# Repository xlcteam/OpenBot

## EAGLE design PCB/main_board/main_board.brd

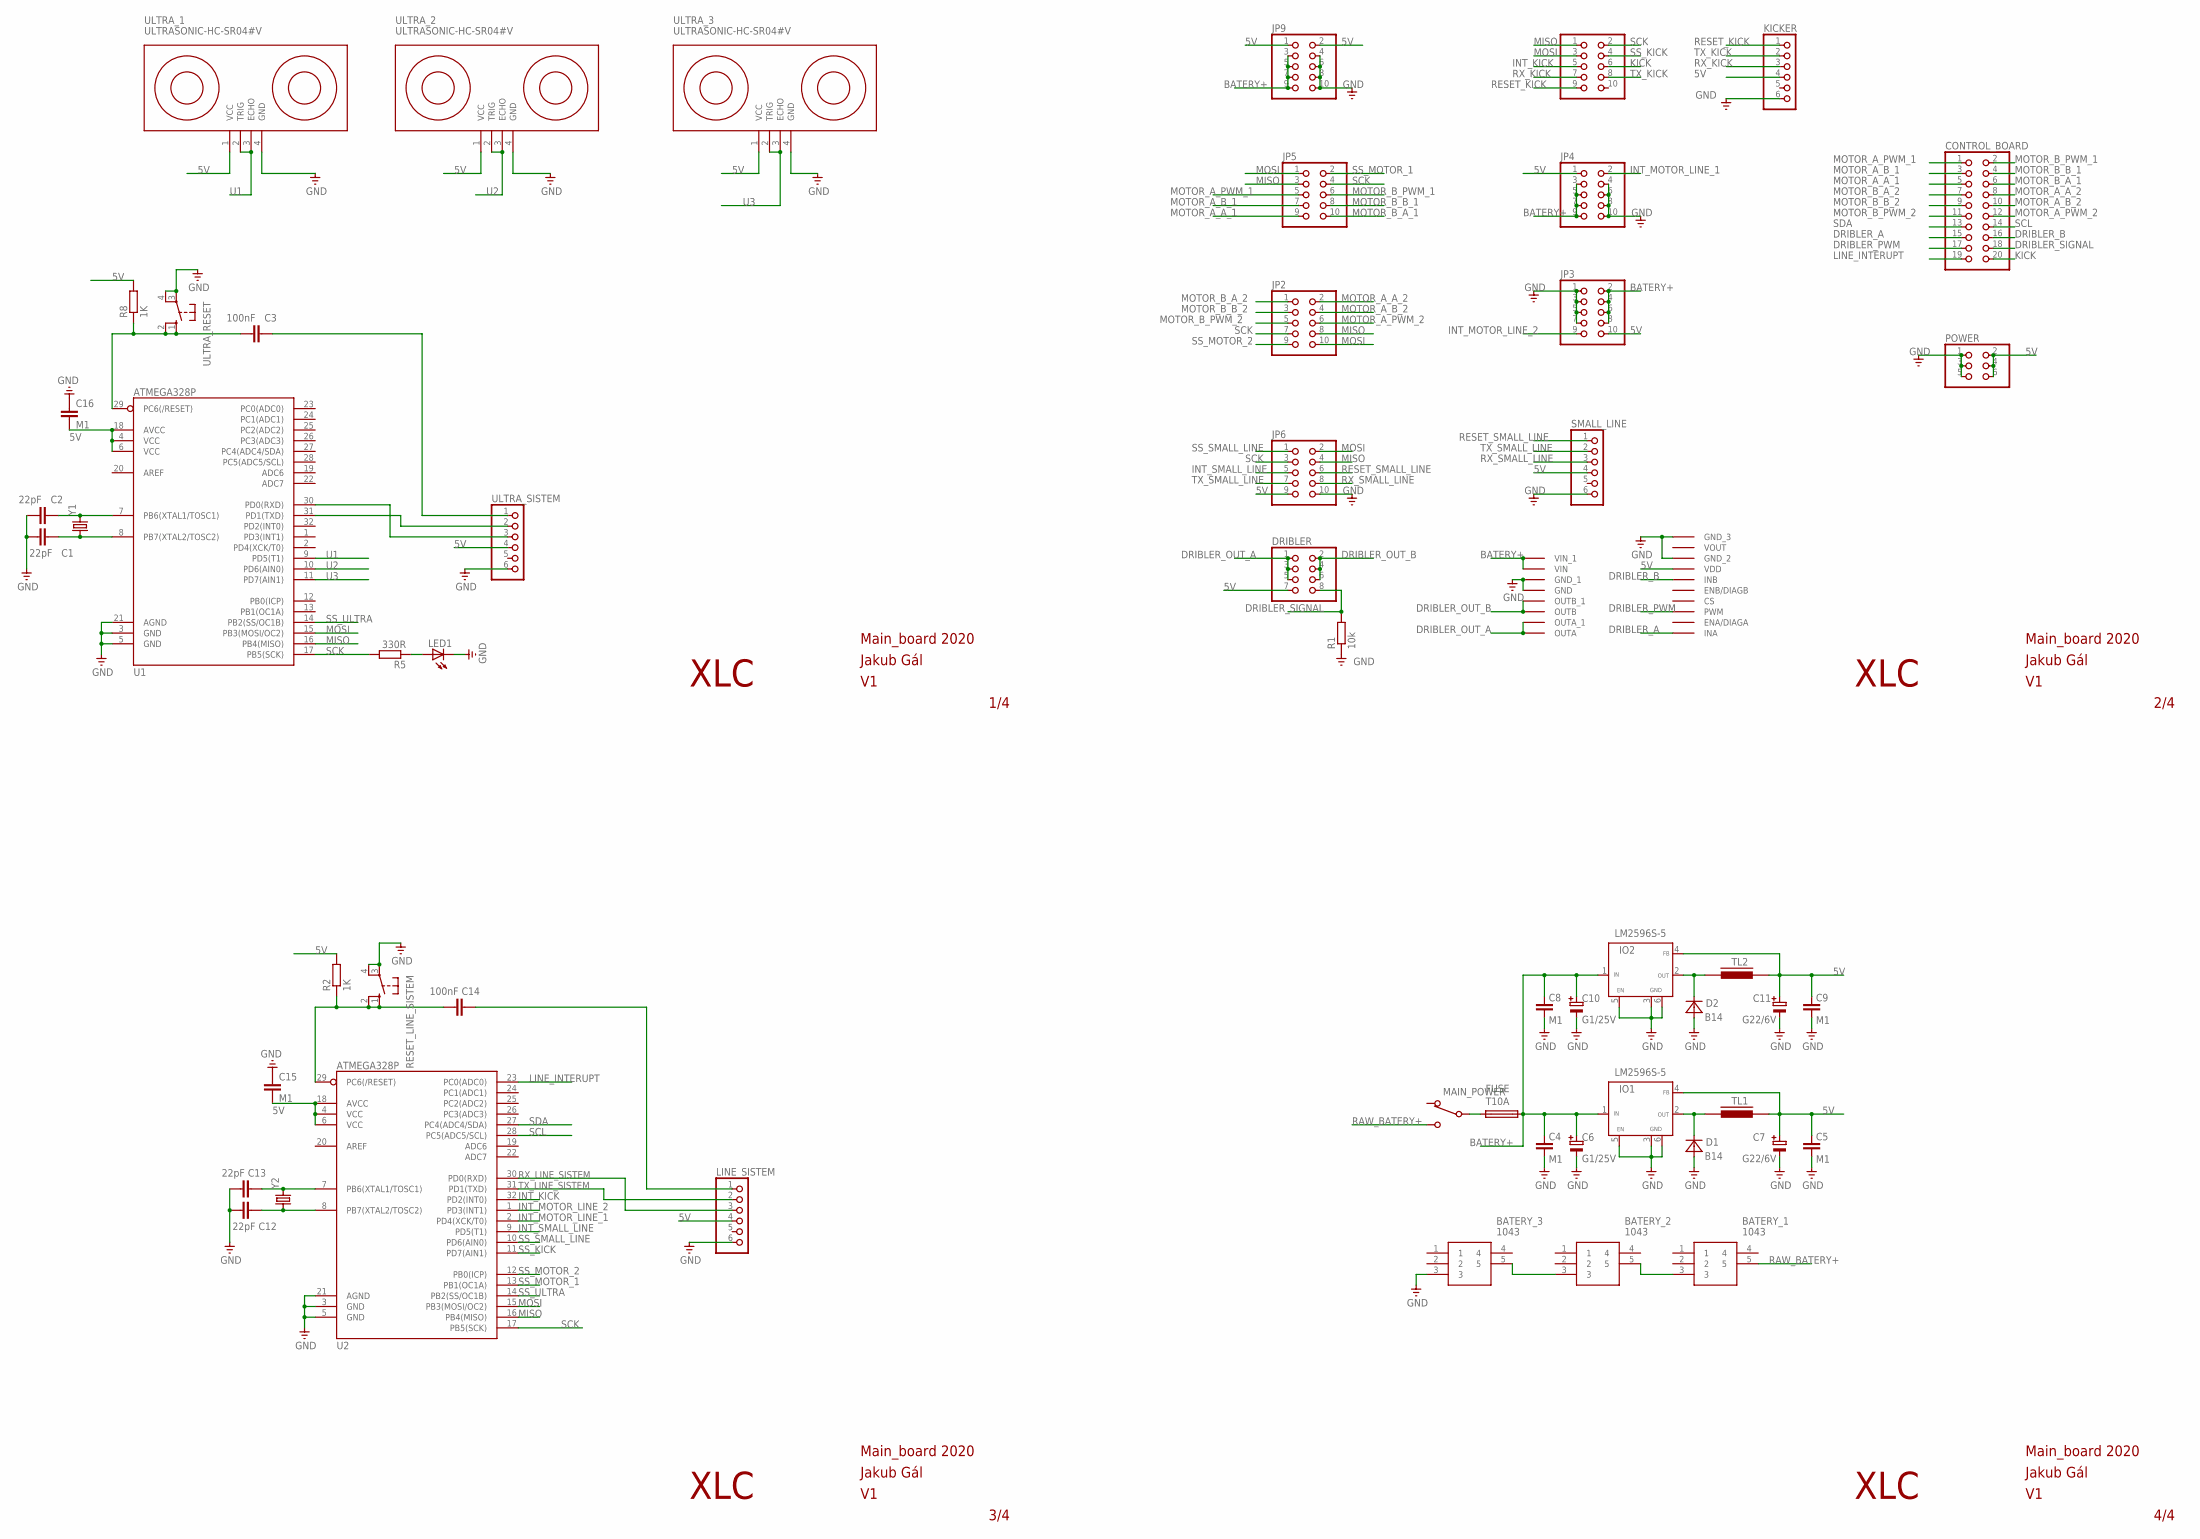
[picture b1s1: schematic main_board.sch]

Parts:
BATERY_1, BATERY_2, BATERY_3: 1043
C1, C2, C12, C13: 22pF; C0603
C3, C14: 100nF; C0603
C4, C5, C8, C9: M1; SMD-1206
C6, C10: G1/25V; SMD-ELE-D
C7, C11: G22/6V; SMD-ELE-D
C15, C16: M1; C0603
CONTROL_BOARD: PINHD-2X10_2.54-SMD; 2X10SMD
D1, D2: B14; D-3,6X5,5
DRIBLER: PINHD-2X4_2.54-SMD; 2X04SMD
FUSE: T10A; SH22,5A
IO1, IO2: LM2596S-5; TO263-5
JP2, JP3, JP4, JP5, JP6, JP8, JP9: PINHD-2X5_2.54-SMD; 2X05SMD
KICKER: PINHD-1X6; 1X06
LED1: LEDCHIPLED_0603; CHIPLED_0603
LINE_SISTEM: PINHD-1X6; 1X06
MAIN_POWER: PREP-1PB; P-B069B
POWER: PINHD-2X3_2.54-SMD; 2X03SMD
R1: 10k; R0603
R2, R8: 1K; R0603
R5: 330R; R0603
RESET_LINE_SISTEM: 10-XX; B3F-10XX
SMALL_LINE: PINHD-1X6; 1X06
TL1, TL2: INDUK-TLSMD1; INDUK-TL
U1, U2: ATMEGA328P; TQFP32-08
U$4: MOTOR_DRIVER
ULTRA_1, ULTRA_2, ULTRA_3: ULTRASONIC-HC-SR04#V
ULTRA_RESET: 10-XX; B3F-10XX
ULTRA_SISTEM: PINHD-1X6; 1X06
Y1, Y2: CRYSTALHC49US; HC49US

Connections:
DRIBLER_A: CONTROL_BOARD.15, U$4.INA
DRIBLER_B: CONTROL_BOARD.16, U$4.INB
DRIBLER_OUT_A: DRIBLER.1, DRIBLER.3, DRIBLER.5, U$4.OUTA, U$4.OUTA_1
DRIBLER_OUT_B: DRIBLER.2, DRIBLER.4, DRIBLER.6, U$4.OUTB, U$4.OUTB_1
DRIBLER_PWM: CONTROL_BOARD.17, U$4.PWM
DRIBLER_SIGNAL: CONTROL_BOARD.18, DRIBLER.8, R1.2
INT_MOTOR_LINE_1: JP4.2, U2.2 (PD4(XCK/T0))
INT_MOTOR_LINE_2: JP3.9, U2.1 (PD3(INT1))
INT_SMALL_LINE: JP6.5, U2.9 (PD5(T1))
LINE_INTERUPT: CONTROL_BOARD.19, U2.23 (PC0(ADC0))
MOTOR_A_A_1: CONTROL_BOARD.5, JP5.9
MOTOR_A_A_2: CONTROL_BOARD.8, JP2.2
MOTOR_A_B_1: CONTROL_BOARD.3, JP5.7
MOTOR_A_B_2: CONTROL_BOARD.10, JP2.4
MOTOR_A_PWM_1: CONTROL_BOARD.1, JP5.5
MOTOR_A_PWM_2: CONTROL_BOARD.12, JP2.6
MOTOR_B_A_1: CONTROL_BOARD.6, JP5.10
MOTOR_B_A_2: CONTROL_BOARD.7, JP2.1
MOTOR_B_B_1: CONTROL_BOARD.4, JP5.8
MOTOR_B_B_2: CONTROL_BOARD.9, JP2.3
MOTOR_B_PWM_1: CONTROL_BOARD.2, JP5.6
MOTOR_B_PWM_2: CONTROL_BOARD.11, JP2.5
unnamed: BATERY_1.3, BATERY_2.5
unnamed: BATERY_2.3, BATERY_3.5
unnamed: D2.K, IO2.2 (OUT), TL2.1
unnamed: FUSE.1, MAIN_POWER.2 (2-COM)
unnamed: C13.2, U2.7 (PB6(XTAL1/TOSC1)), Y2.2
unnamed: D1.K, IO1.2 (OUT), TL1.1
unnamed: C2.2, U1.7 (PB6(XTAL1/TOSC1)), Y1.2
unnamed: C1.2, U1.8 (PB7(XTAL2/TOSC2)), Y1.1
unnamed: C12.2, U2.8 (PB7(XTAL2/TOSC2)), Y2.1
unnamed: C14.2, LINE_SISTEM.1
unnamed: C14.1, R2.1, RESET_LINE_SISTEM.1 (S), RESET_LINE_SISTEM.2 (S1), U2.29 (PC6(/RESET))
unnamed: U1.30 (PD0(RXD)), ULTRA_SISTEM.3
unnamed: U1.31 (PD1(TXD)), ULTRA_SISTEM.2
unnamed: C3.2, ULTRA_SISTEM.1
unnamed: C3.1, R8.1, U1.29 (PC6(/RESET)), ULTRA_RESET.1 (S), ULTRA_RESET.2 (S1)
unnamed: LED1.A, R5.1
RAW_BATERY+: BATERY_1.5, MAIN_POWER.1 (1-OFF)
RESET_SMALL_LINE: JP6.6, SMALL_LINE.1
RX_LINE_SISTEM: LINE_SISTEM.3, U2.30 (PD0(RXD))
RX_SMALL_LINE: JP6.8, SMALL_LINE.3
SCL: CONTROL_BOARD.14, U2.28 (PC5(ADC5/SCL))
SDA: CONTROL_BOARD.13, U2.27 (PC4(ADC4/SDA))
SS_MOTOR_1: JP5.2, U2.13 (PB1(OC1A))
SS_MOTOR_2: JP2.9, U2.12 (PB0(ICP))
SS_SMALL_LINE: JP6.1, U2.10 (PD6(AIN0))
SS_ULTRA: U1.14 (PB2(SS/OC1B)), U2.14 (PB2(SS/OC1B))
TX_LINE_SISTEM: LINE_SISTEM.2, U2.31 (PD1(TXD))
TX_SMALL_LINE: JP6.7, SMALL_LINE.2
U1: U1.9 (PD5(T1)), ULTRA_1.2 (TRIG), ULTRA_1.3 (ECHO)
U2: U1.10 (PD6(AIN0)), ULTRA_2.2 (TRIG), ULTRA_2.3 (ECHO)
U3: U1.11 (PD7(AIN1)), ULTRA_3.2 (TRIG), ULTRA_3.3 (ECHO)

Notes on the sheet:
1/4
2/4
3/4
4/4
XLC
Main_board 2020
Jakub Gál

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
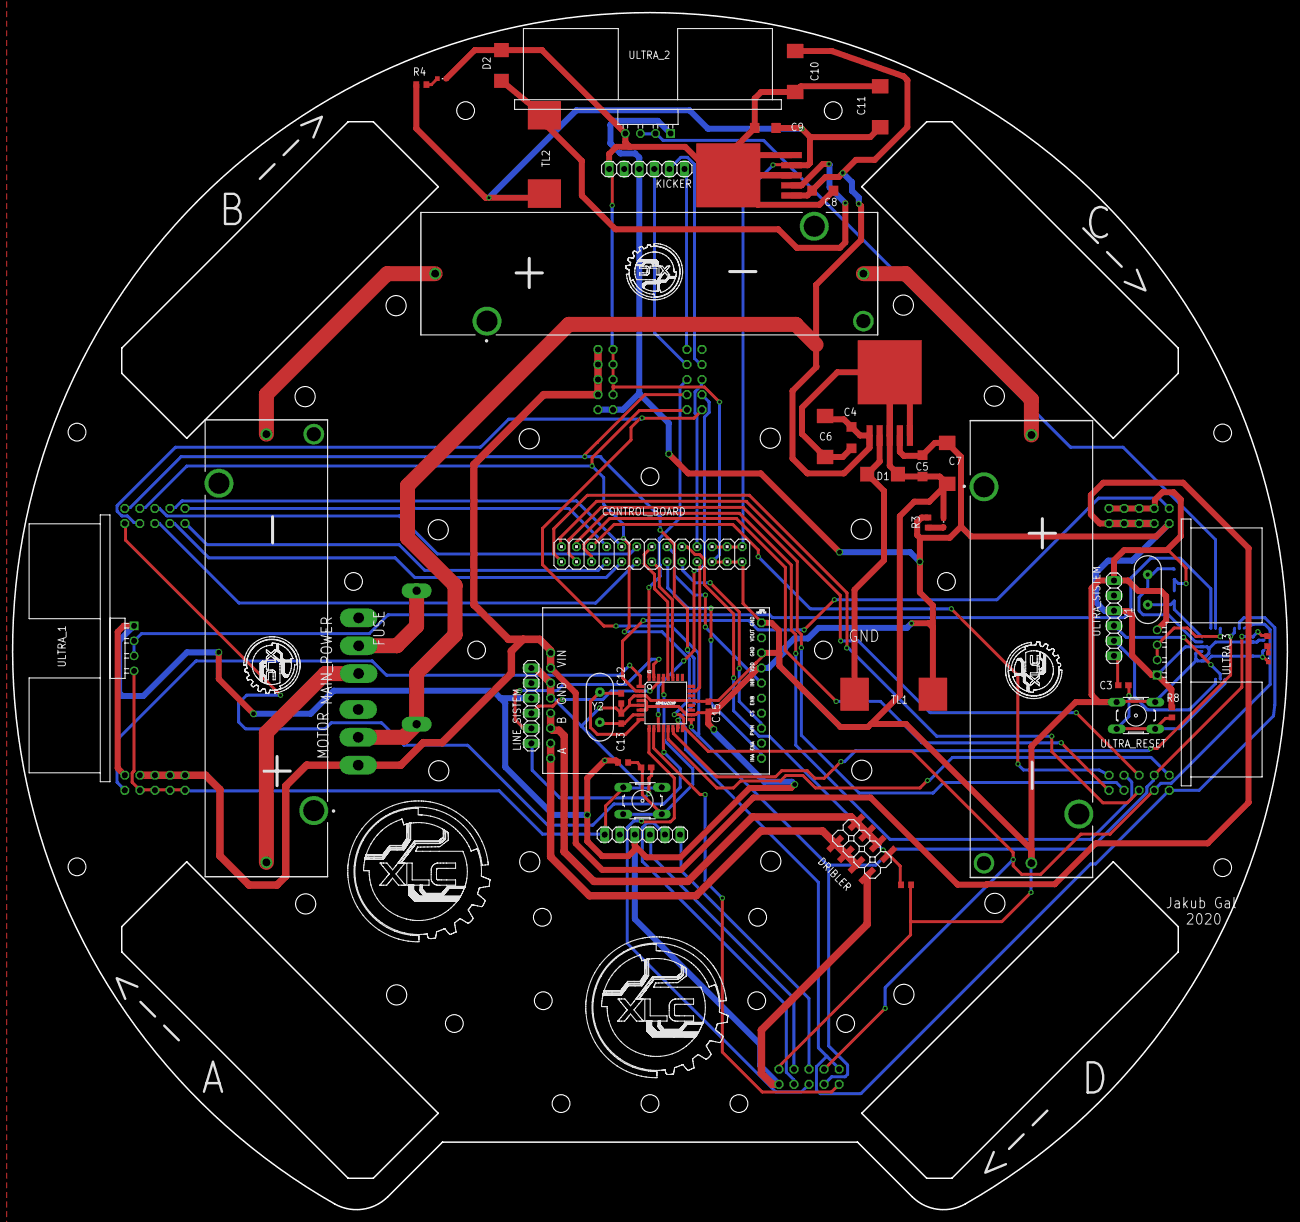
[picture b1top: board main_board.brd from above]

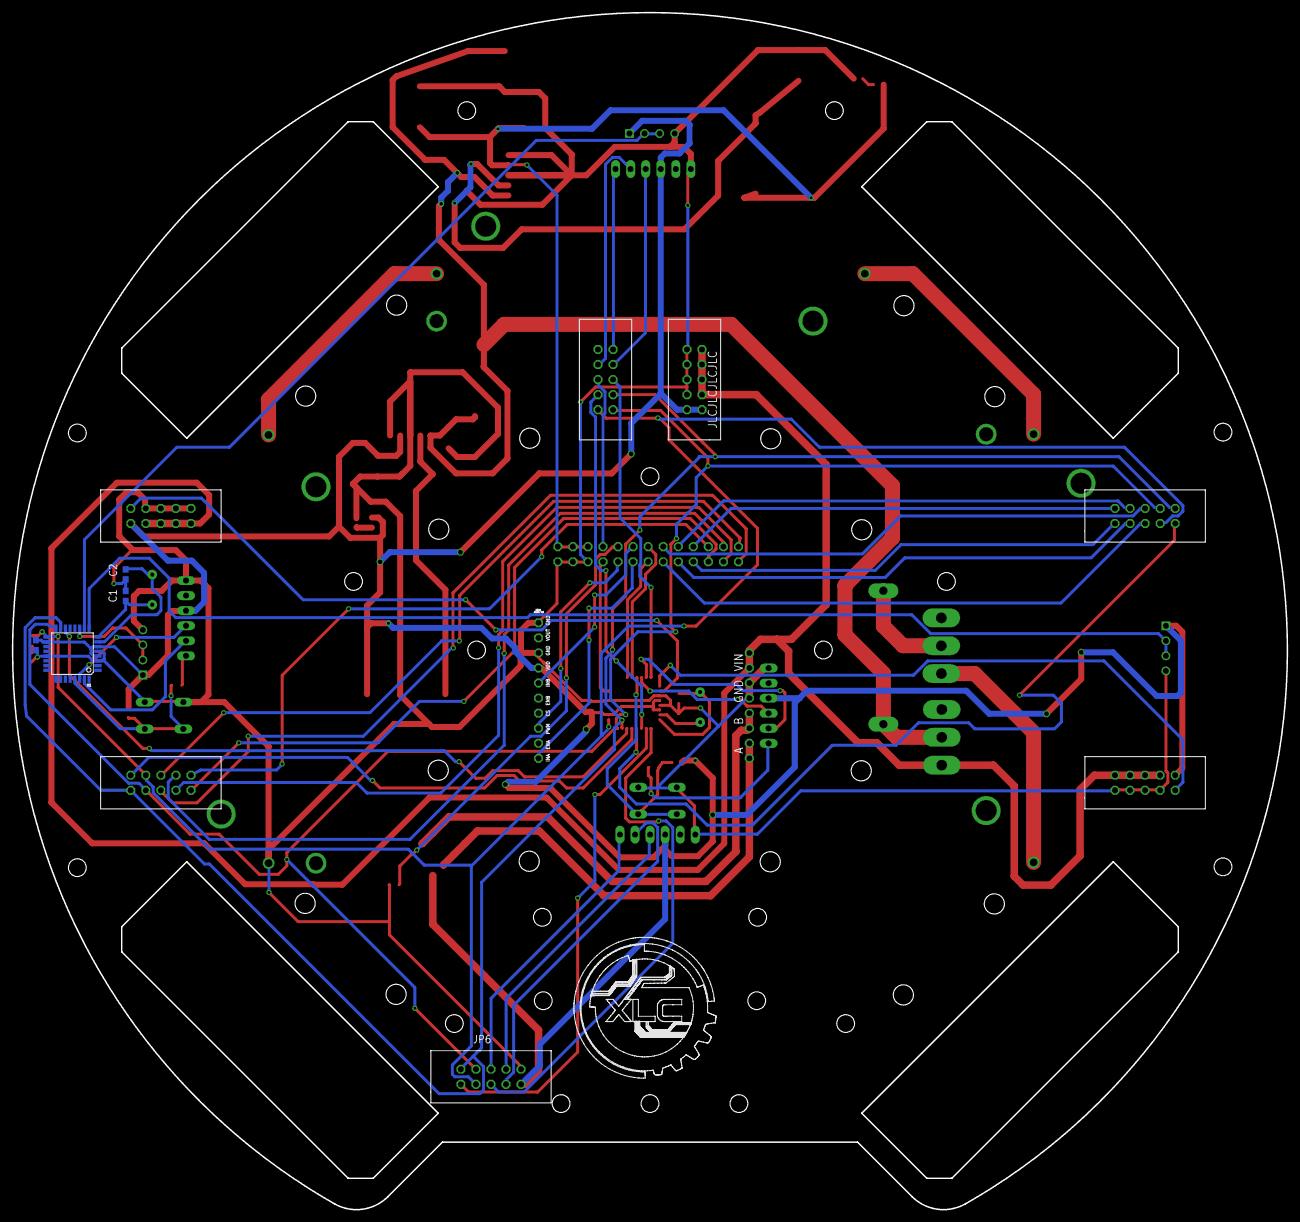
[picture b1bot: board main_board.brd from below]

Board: 2 copper layers, 215.0 x 201.9 mm, 60 parts (11 on the bottom side), 69 nets.

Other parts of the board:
ARDUINO_LED: LEDCHIPLED_0603; CHIPLED_0603
JP1: 2X05_IDC
MOTOR: P-B069B
R3, R4: 330R; R0603
RPI_LED: LEDCHIPLED_0603; CHIPLED_0603

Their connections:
unnamed: ARDUINO_LED.A, R3.1
unnamed: R4.1, RPI_LED.A

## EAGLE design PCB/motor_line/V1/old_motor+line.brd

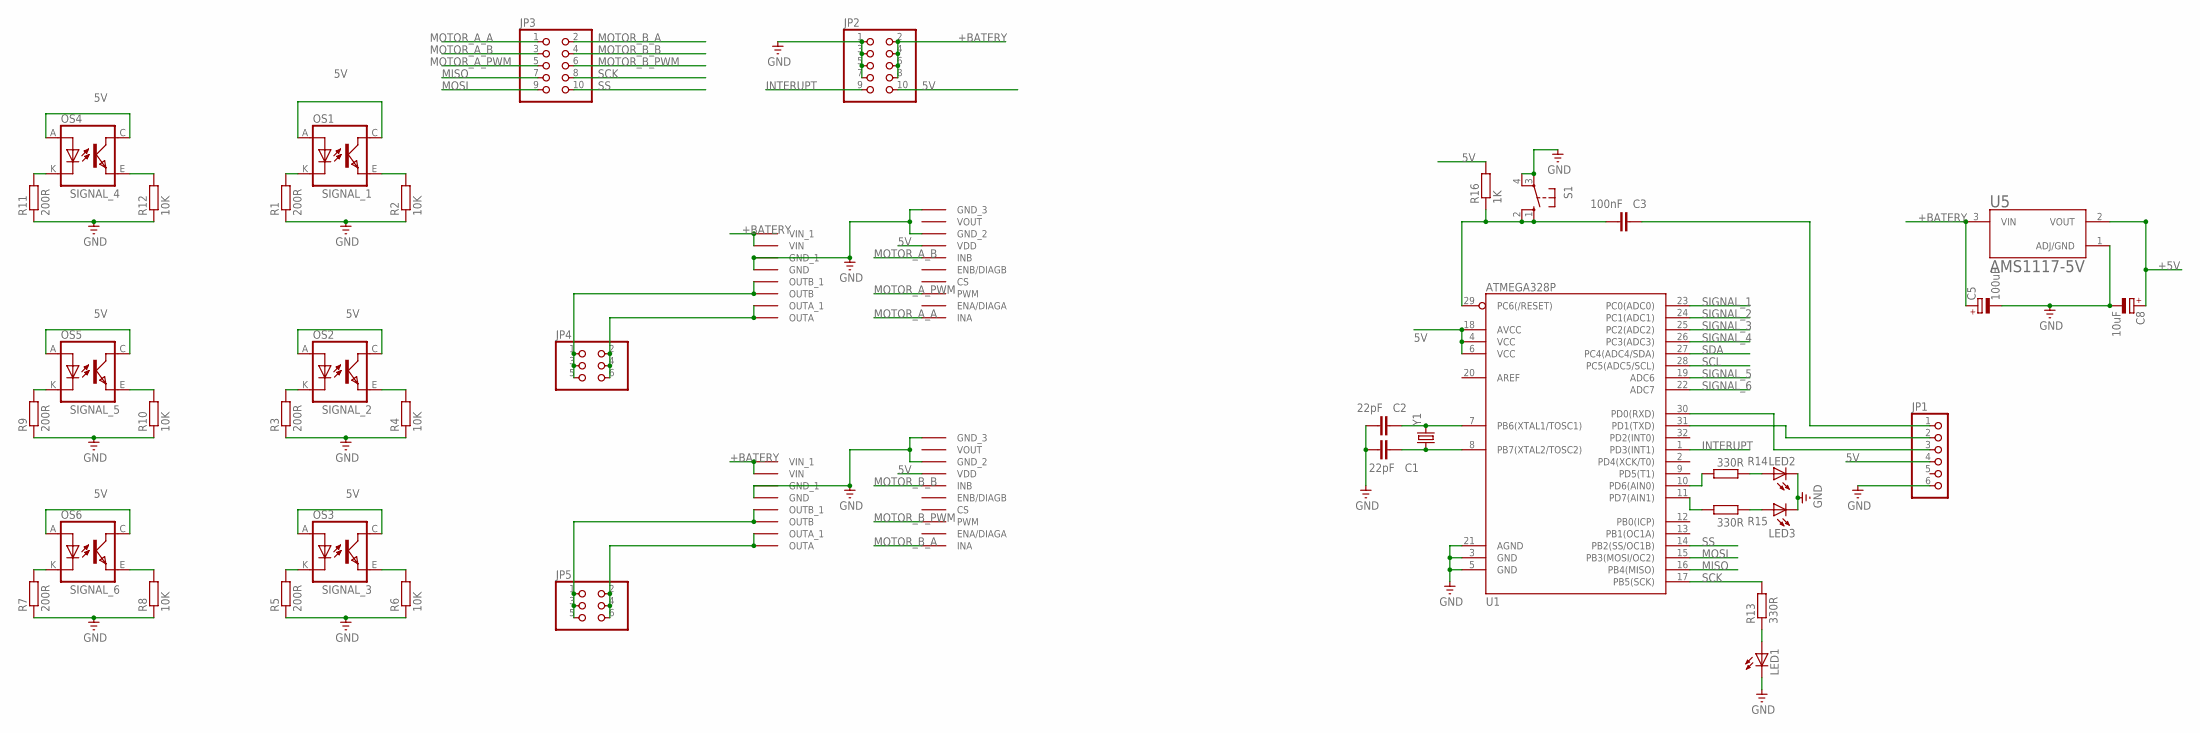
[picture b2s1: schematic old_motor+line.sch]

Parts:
C1, C2: 22pF; C0603
C3: 100nF; C0603
C5: 100uF; UD-6,3X7,7_NICHICON
C8: 10uF; UD-4X5,8_NICHICON
JP1: PINHD-1X6/90; 1X06/90
JP2, JP3: PINHD-2X5; 2X05
JP4, JP5: PINHD-2X3; 2X03
LED1, LED2, LED3: LEDCHIPLED_0603; CHIPLED_0603
OS1, OS2, OS3, OS4, OS5, OS6: TCRT5000
R1, R3, R5, R7, R9, R11: 200R; R0603
R2, R4, R6, R8, R10, R12: 10K; R0603
R13, R14, R15: 330R; R0603
R16: 1K; R0603
S1: 10-XX; B3F-10XX
U1: ATMEGA328P; TQFP32-08
U5: AMS1117-5V; SOT229P700X180-4N
U$1, U$2: MOTOR_DRIVER
Y1: CRYSTALHC49US; HC49US

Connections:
5V: JP1.4, JP2.10, OS1.A (ANODE), OS1.C (COLLECTOR), OS2.A (ANODE), OS2.C (COLLECTOR), OS3.A (ANODE), OS3.C (COLLECTOR), OS4.A (ANODE), OS4.C (COLLECTOR), OS5.A (ANODE), OS5.C (COLLECTOR), OS6.A (ANODE), OS6.C (COLLECTOR), R16.2, U1.4 (VCC), U1.6 (VCC), U1.18 (AVCC), U$1.VDD, U$2.VDD
+5V: C8.+, U5.2 (VOUT)
+BATERY: C5.+, JP2.2, JP2.4, JP2.6, JP2.8, U5.3 (VIN), U$1.VIN, U$1.VIN_1, U$2.VIN, U$2.VIN_1
GND: C1.1, C2.1, C5.-, C8.-, JP1.6, JP2.1, JP2.3, JP2.5, JP2.7, LED1.C, LED2.C, LED3.C, R1.1, R2.1, R3.1, R4.1, R5.1, R6.1, R7.1, R8.1, R9.1, R10.1, R11.1, R12.1, S1.3, S1.4 (P1), U1.3 (GND), U1.5 (GND), U1.21 (AGND), U5.1 (ADJ/GND), U$1.GND, U$1.GND_1, U$1.GND_2, U$1.GND_3, U$2.GND, U$2.GND_1, U$2.GND_2, U$2.GND_3
INTERUPT: JP2.9, U1.1 (PD3(INT1))
MISO: JP3.7, U1.16 (PB4(MISO))
MOSI: JP3.9, U1.15 (PB3(MOSI/OC2))
MOTOR_1_1: JP4.1, JP4.3, JP4.5, U$1.OUTB, U$1.OUTB_1
MOTOR_1_2: JP4.2, JP4.4, JP4.6, U$1.OUTA, U$1.OUTA_1
MOTOR_2_1: JP5.2, JP5.4, JP5.6, U$2.OUTA, U$2.OUTA_1
MOTOR_2_2: JP5.1, JP5.3, JP5.5, U$2.OUTB, U$2.OUTB_1
MOTOR_A_A: JP3.1, U$1.INA
MOTOR_A_B: JP3.3, U$1.INB
MOTOR_A_PWM: JP3.5, U$1.PWM
MOTOR_B_A: JP3.2, U$2.INA
MOTOR_B_B: JP3.4, U$2.INB
MOTOR_B_PWM: JP3.6, U$2.PWM
unnamed: OS1.K (CATHODE), R1.2
unnamed: OS2.K (CATHODE), R3.2
unnamed: OS3.K (CATHODE), R5.2
unnamed: OS6.K (CATHODE), R7.2
unnamed: OS5.K (CATHODE), R9.2
unnamed: OS4.K (CATHODE), R11.2
unnamed: C2.2, U1.7 (PB6(XTAL1/TOSC1)), Y1.2
unnamed: C1.2, U1.8 (PB7(XTAL2/TOSC2)), Y1.1
unnamed: JP1.3, U1.30 (PD0(RXD))
unnamed: JP1.2, U1.31 (PD1(TXD))
unnamed: C3.2, JP1.1
unnamed: C3.1, R16.1, S1.1 (S), S1.2 (S1), U1.29 (PC6(/RESET))
unnamed: LED1.A, R13.1
unnamed: LED2.A, R14.1
unnamed: R15.2, U1.11 (PD7(AIN1))
unnamed: LED3.A, R15.1
unnamed: R14.2, U1.10 (PD6(AIN0))
SCK: JP3.8, R13.2, U1.17 (PB5(SCK))
SCL: U1.28 (PC5(ADC5/SCL))
SDA: U1.27 (PC4(ADC4/SDA))
SIGNAL_1: OS1.E (EMITTER), R2.2, U1.23 (PC0(ADC0))
SIGNAL_2: OS2.E (EMITTER), R4.2, U1.24 (PC1(ADC1))
SIGNAL_3: OS3.E (EMITTER), R6.2, U1.25 (PC2(ADC2))
SIGNAL_4: OS4.E (EMITTER), R12.2, U1.26 (PC3(ADC3))
SIGNAL_5: OS5.E (EMITTER), R10.2, U1.19 (ADC6)
SIGNAL_6: OS6.E (EMITTER), R8.2, U1.22 (ADC7)
SS: JP3.10, U1.14 (PB2(SS/OC1B))

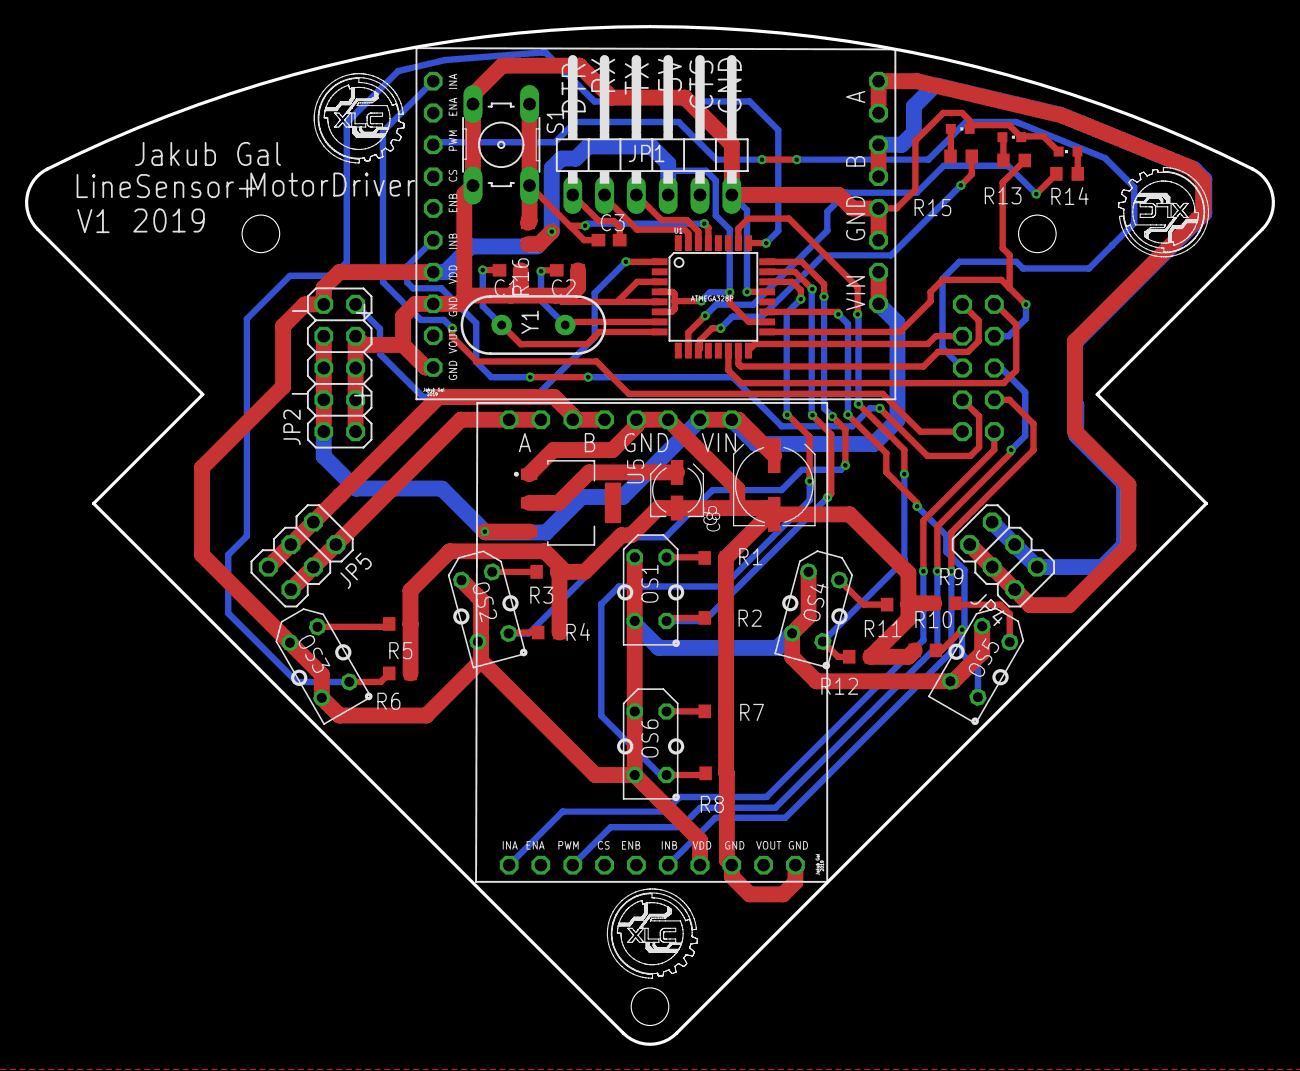
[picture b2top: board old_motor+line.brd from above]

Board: 2 copper layers, 99.5 x 81.3 mm, 41 parts (1 on the bottom side), 42 nets.

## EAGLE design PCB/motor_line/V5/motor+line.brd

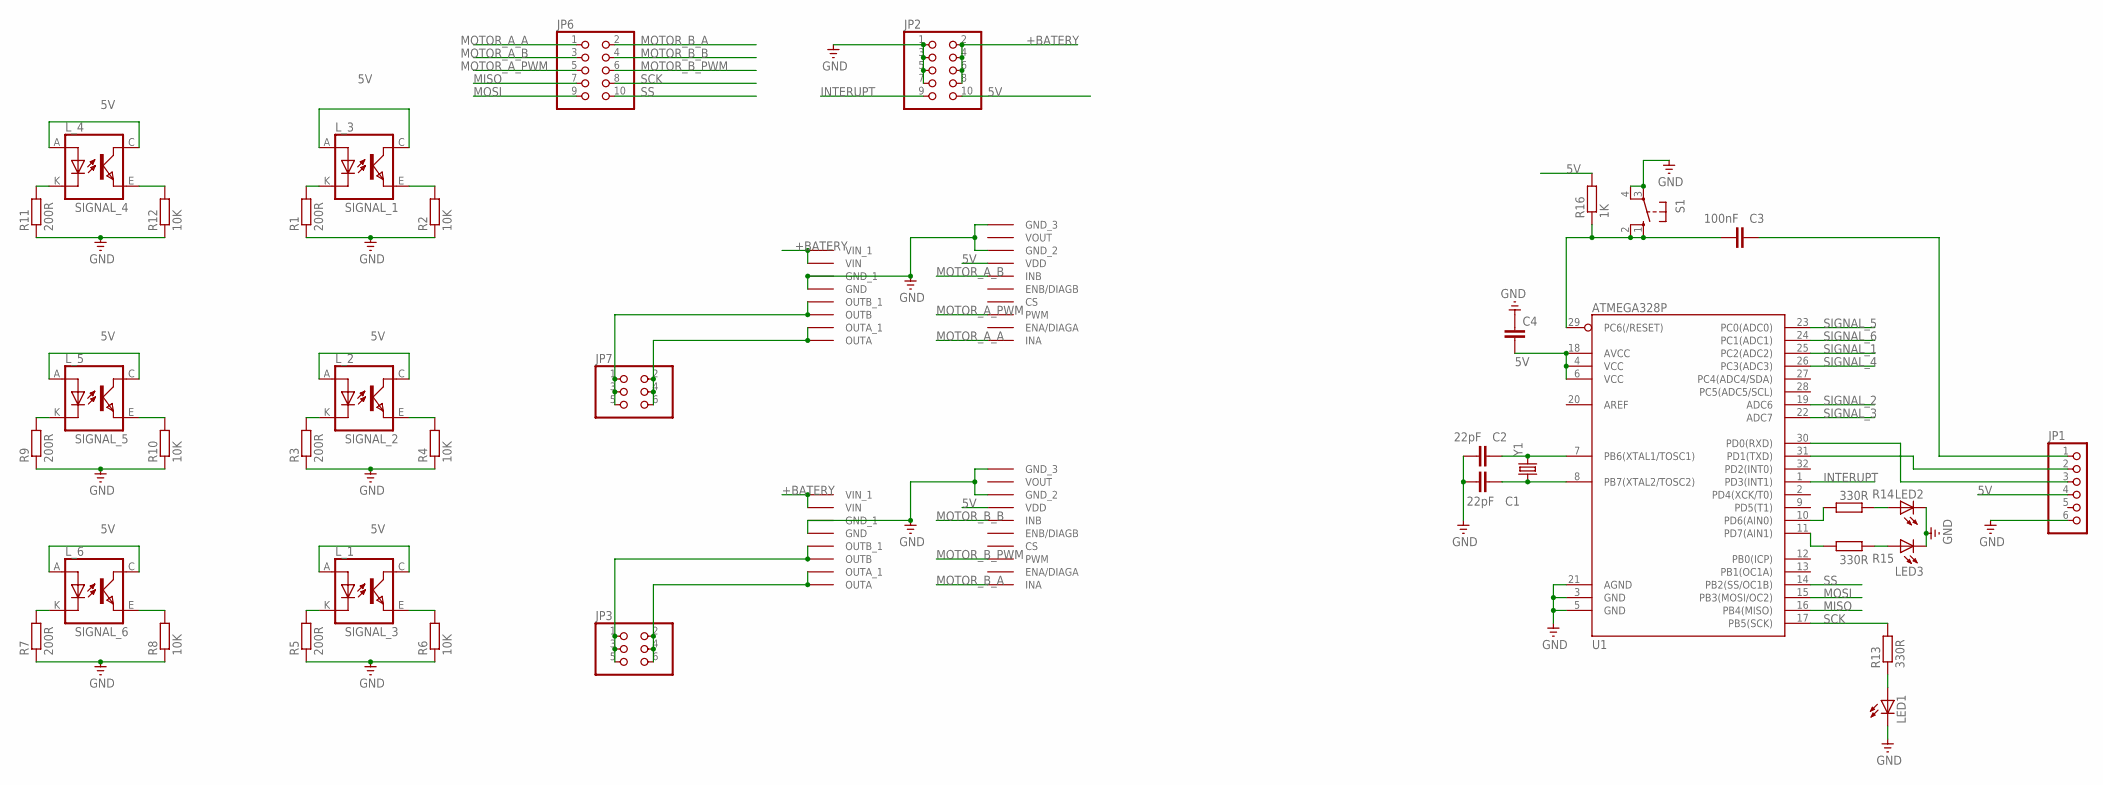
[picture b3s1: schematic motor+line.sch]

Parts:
C1, C2: 22pF; C0603
C3: 100nF; C0603
C4: C-EUC0603; C0603
JP1: PINHD-1X6/90; 1X06/90
JP2, JP6: PINHD-2X5IDC; 2X05_IDC
JP3, JP7: PINHD-2X3IDC; 2X03_IDC
LED1, LED2, LED3: LEDCHIPLED_0603; CHIPLED_0603
L_1, L_2, L_3, L_4, L_5, L_6: TCRT5000
R1, R3, R5, R7, R9, R11: 200R; R0603
R2, R4, R6, R8, R10, R12: 10K; R0603
R13, R14, R15: 330R; R0603
R16: 1K; R0603
S1: 10-XX; B3F-10XX
U1: ATMEGA328P; TQFP32-08
U$1, U$2: MOTOR_DRIVER
Y1: CRYSTALHC49US; HC49US

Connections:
5V: C4.2, JP1.4, JP2.10, L_1.A (ANODE), L_1.C (COLLECTOR), L_2.A (ANODE), L_2.C (COLLECTOR), L_3.A (ANODE), L_3.C (COLLECTOR), L_4.A (ANODE), L_4.C (COLLECTOR), L_5.A (ANODE), L_5.C (COLLECTOR), L_6.A (ANODE), L_6.C (COLLECTOR), R16.2, U1.4 (VCC), U1.6 (VCC), U1.18 (AVCC), U$1.VDD, U$2.VDD
+BATERY: JP2.2, JP2.4, JP2.6, JP2.8, U$1.VIN, U$1.VIN_1, U$2.VIN, U$2.VIN_1
GND: C1.1, C2.1, C4.1, JP1.6, JP2.1, JP2.3, JP2.5, JP2.7, LED1.C, LED2.C, LED3.C, R1.1, R2.1, R3.1, R4.1, R5.1, R6.1, R7.1, R8.1, R9.1, R10.1, R11.1, R12.1, S1.3, S1.4 (P1), U1.3 (GND), U1.5 (GND), U1.21 (AGND), U$1.GND, U$1.GND_1, U$1.GND_2, U$1.GND_3, U$2.GND, U$2.GND_1, U$2.GND_2, U$2.GND_3
INTERUPT: JP2.9, U1.1 (PD3(INT1))
MISO: JP6.7, U1.16 (PB4(MISO))
MOSI: JP6.9, U1.15 (PB3(MOSI/OC2))
MOTOR_1_1: JP7.1, JP7.3, JP7.5, U$1.OUTB, U$1.OUTB_1
MOTOR_1_2: JP7.2, JP7.4, JP7.6, U$1.OUTA, U$1.OUTA_1
MOTOR_2_1: JP3.2, JP3.4, JP3.6, U$2.OUTA, U$2.OUTA_1
MOTOR_2_2: JP3.1, JP3.3, JP3.5, U$2.OUTB, U$2.OUTB_1
MOTOR_A_A: JP6.1, U$1.INA
MOTOR_A_B: JP6.3, U$1.INB
MOTOR_A_PWM: JP6.5, U$1.PWM
MOTOR_B_A: JP6.2, U$2.INA
MOTOR_B_B: JP6.4, U$2.INB
MOTOR_B_PWM: JP6.6, U$2.PWM
unnamed: L_3.K (CATHODE), R1.2
unnamed: L_2.K (CATHODE), R3.2
unnamed: L_1.K (CATHODE), R5.2
unnamed: L_6.K (CATHODE), R7.2
unnamed: L_5.K (CATHODE), R9.2
unnamed: L_4.K (CATHODE), R11.2
unnamed: C2.2, U1.7 (PB6(XTAL1/TOSC1)), Y1.2
unnamed: C1.2, U1.8 (PB7(XTAL2/TOSC2)), Y1.1
unnamed: JP1.3, U1.30 (PD0(RXD))
unnamed: JP1.2, U1.31 (PD1(TXD))
unnamed: C3.2, JP1.1
unnamed: C3.1, R16.1, S1.1 (S), S1.2 (S1), U1.29 (PC6(/RESET))
unnamed: LED1.A, R13.1
unnamed: LED2.A, R14.1
unnamed: R15.2, U1.11 (PD7(AIN1))
unnamed: LED3.A, R15.1
unnamed: R14.2, U1.10 (PD6(AIN0))
SCK: JP6.8, R13.2, U1.17 (PB5(SCK))
SIGNAL_1: L_3.E (EMITTER), R2.2, U1.25 (PC2(ADC2))
SIGNAL_2: L_2.E (EMITTER), R4.2, U1.19 (ADC6)
SIGNAL_3: L_1.E (EMITTER), R6.2, U1.22 (ADC7)
SIGNAL_4: L_4.E (EMITTER), R12.2, U1.26 (PC3(ADC3))
SIGNAL_5: L_5.E (EMITTER), R10.2, U1.23 (PC0(ADC0))
SIGNAL_6: L_6.E (EMITTER), R8.2, U1.24 (PC1(ADC1))
SS: JP6.10, U1.14 (PB2(SS/OC1B))

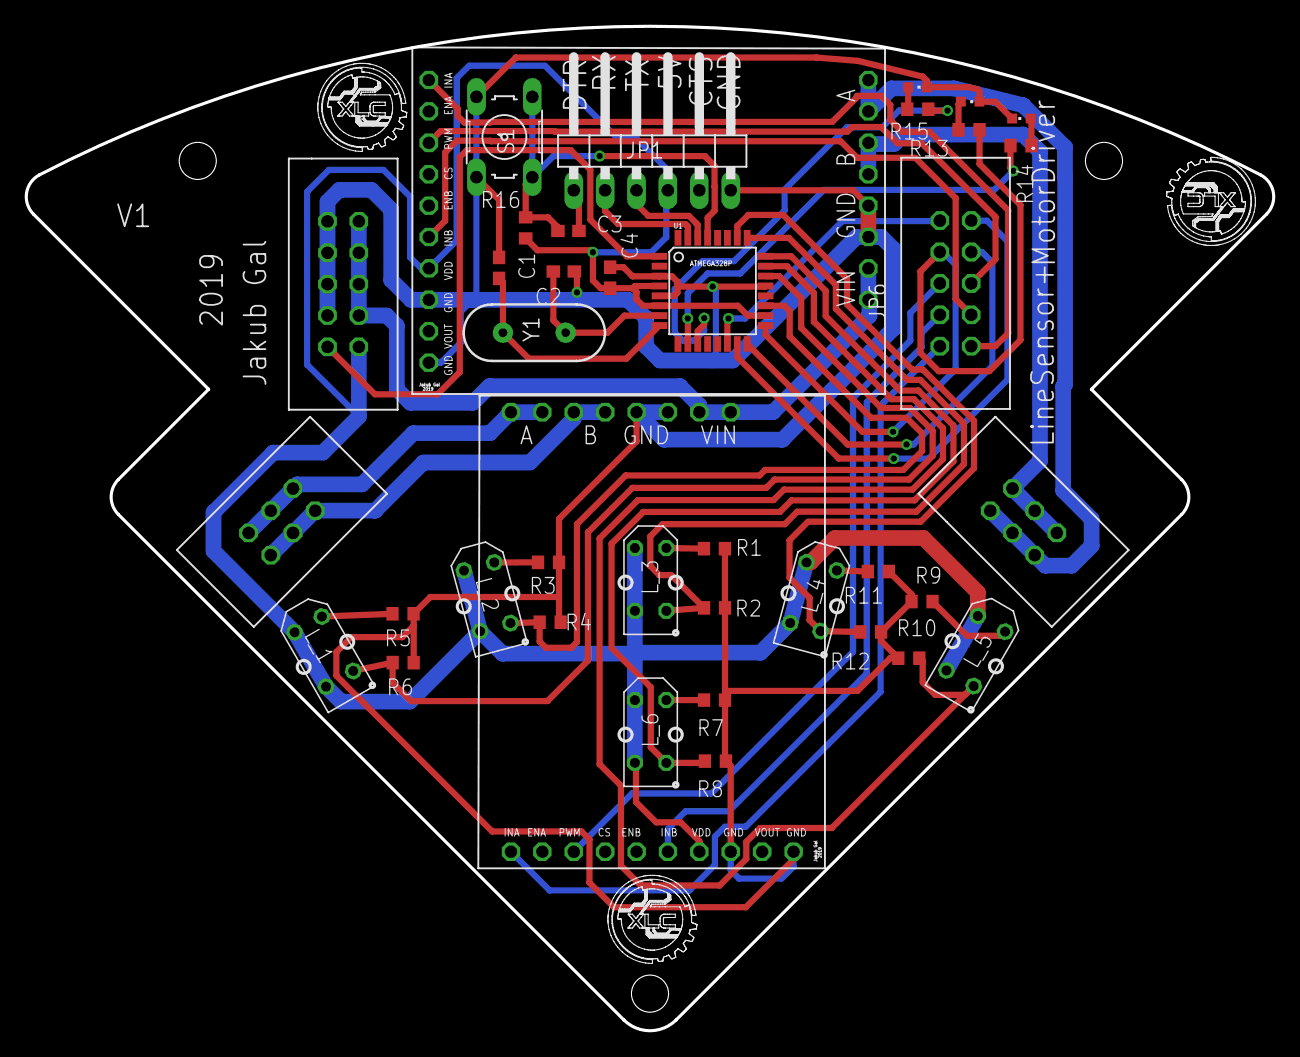
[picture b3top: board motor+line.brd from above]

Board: 2 copper layers, 100.9 x 81.3 mm, 39 parts (0 on the bottom side), 41 nets.

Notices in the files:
parts and their libraries:
diy-modules: Released under the Creative Commons Attribution 4.0 International License: http://creativecommons.org/licenses/by/4.0
SparkFun-DigitalIC: Licensing: CC v3.0 Share-Alike You are welcome to use this library for commercial purposes.
